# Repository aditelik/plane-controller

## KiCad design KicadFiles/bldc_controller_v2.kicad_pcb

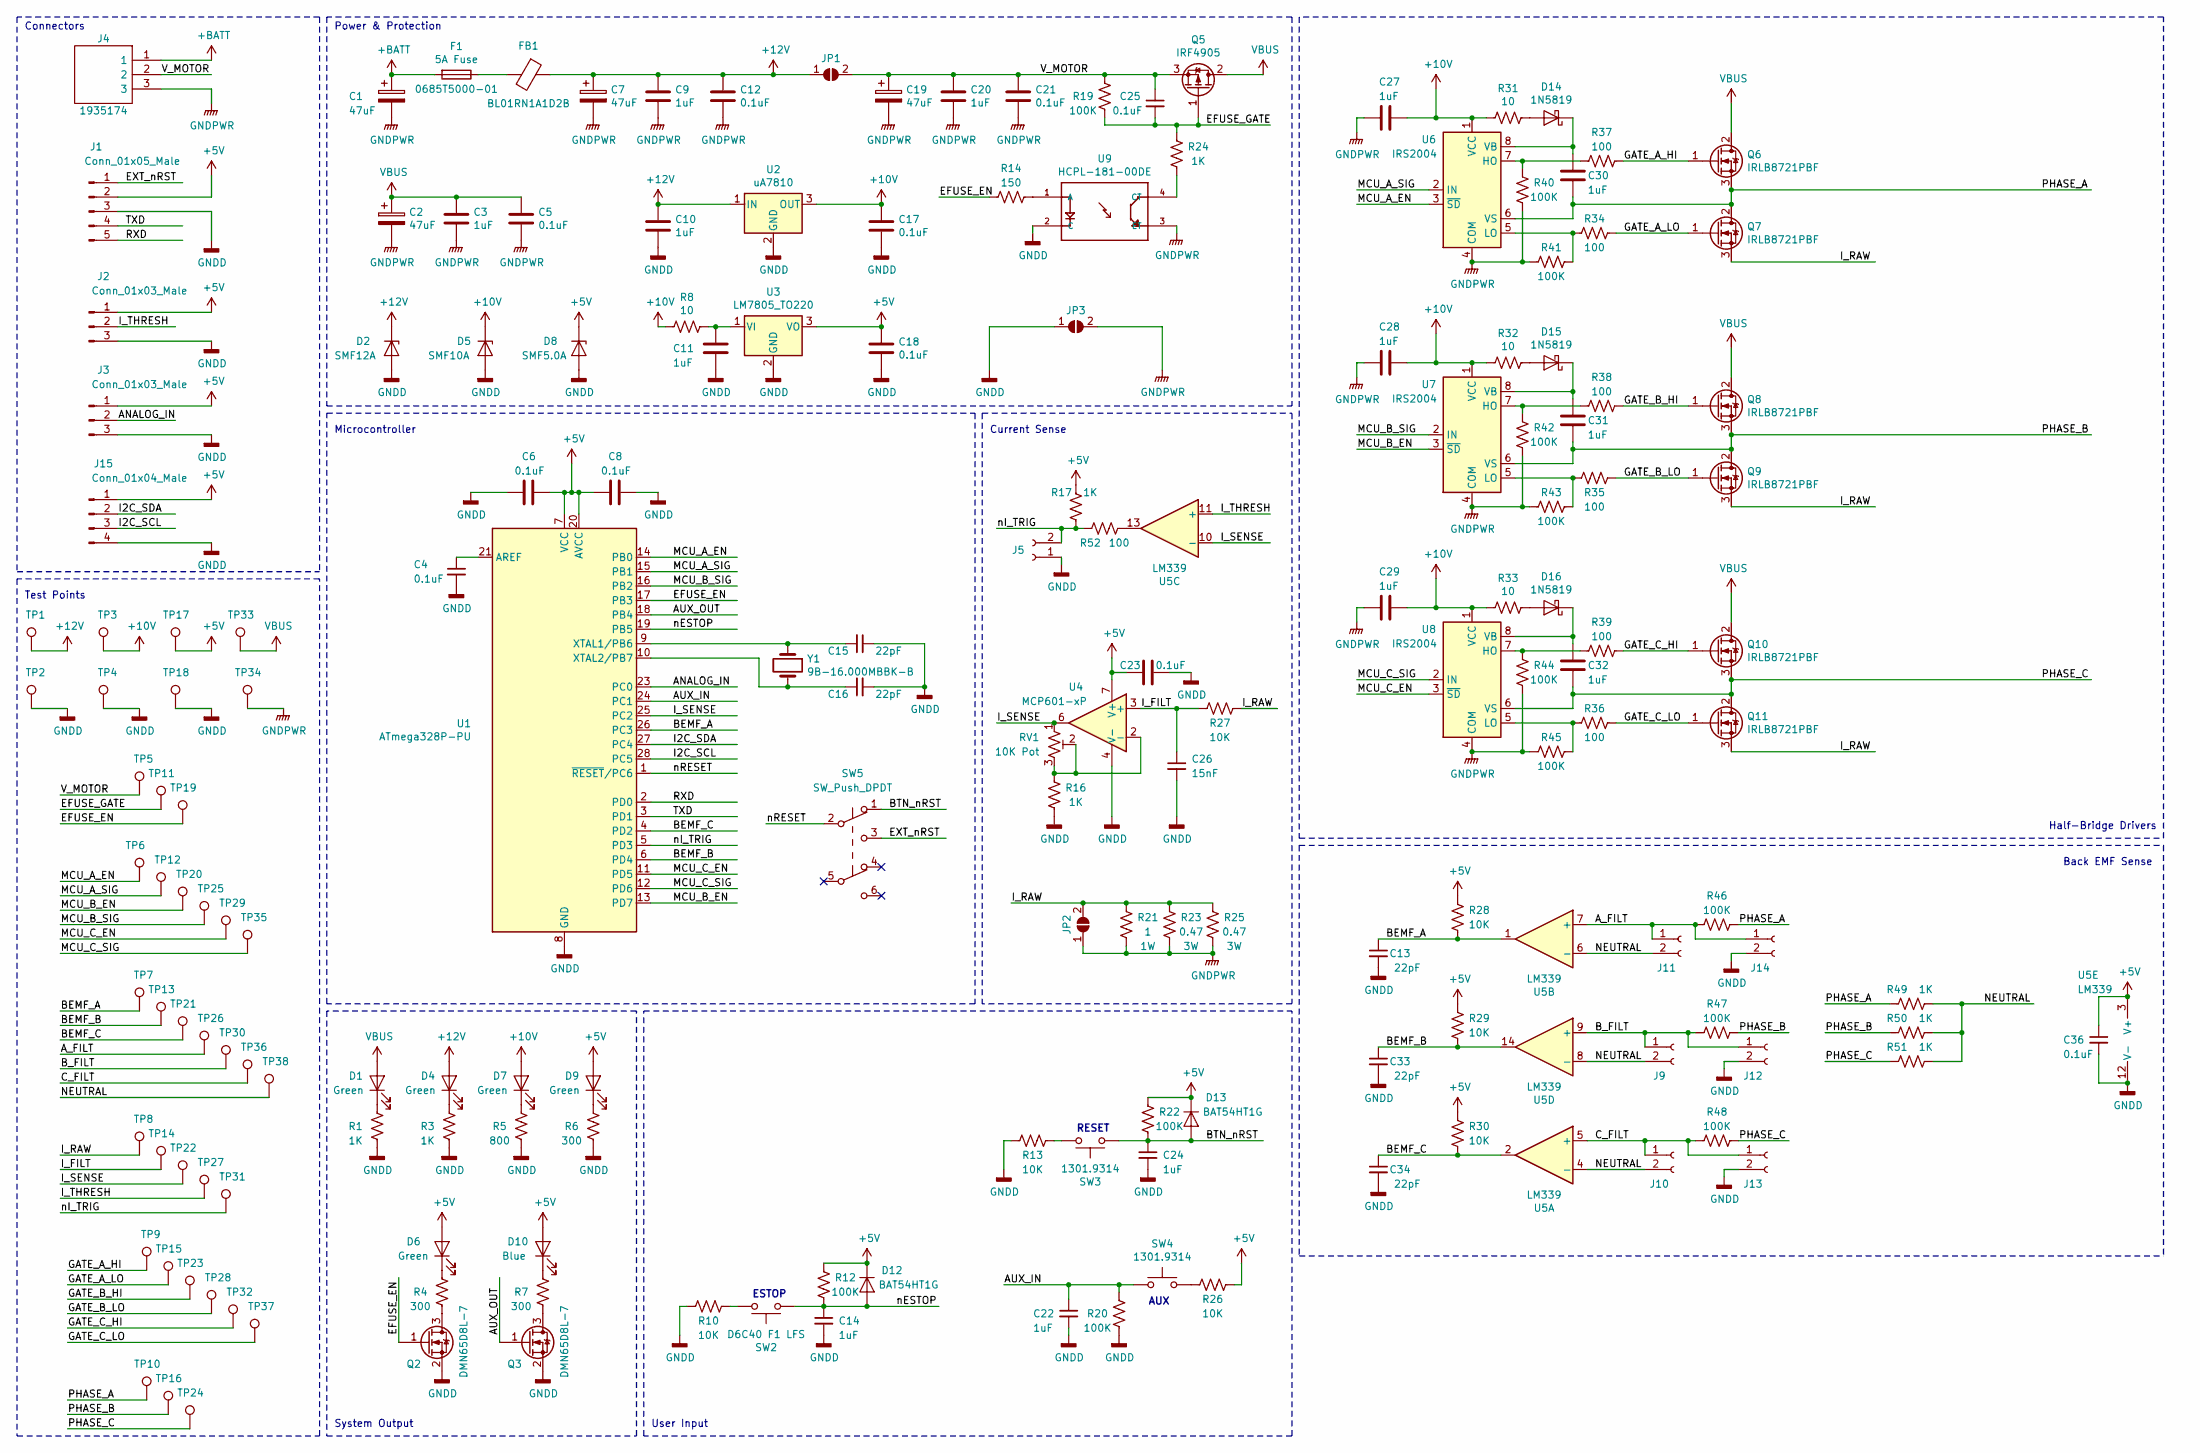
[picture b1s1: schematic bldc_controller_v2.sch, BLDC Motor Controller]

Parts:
C1, C2, C7, C19: 47uF; CP_Radial_D5.0mm_P2.00mm
C3, C9, C10, C11, C14, C20, C22, C24, C27, C28, C29, C30, C31, C32: 1uF; C_0805_2012Metric_Pad1.15x1.40mm_HandSolder
C4, C5, C6, C8, C12, C17, C18, C21, C23, C25, C36: 0.1uF; C_0805_2012Metric_Pad1.15x1.40mm_HandSolder
C13, C15, C16, C33, C34: 22pF; C_0805_2012Metric_Pad1.15x1.40mm_HandSolder
C26: 15nF; C_0805_2012Metric_Pad1.15x1.40mm_HandSolder
D1, D4, D7, D9: LTST-C171GKT; LED_0805_2012Metric_Pad1.15x1.40mm_HandSolder
D2: SMF12A; D_SOD-123F
D5: SMF10A; D_SOD-123F
D6: LTST-C171KRKT; LED_0805_2012Metric_Pad1.15x1.40mm_HandSolder
D8: SMF5.0A; D_SOD-123F
D10: LTST-C171TBKT; LED_0805_2012Metric_Pad1.15x1.40mm_HandSolder
D12, D13: BAT54HT1G; D_SOD-323_HandSoldering
D14, D15, D16: 1N5819; D_SOD-123
F1: 5A Fuse; Fuse_1206_3216Metric_Pad1.42x1.75mm_HandSolder; Part Number 0685T5000-01
FB1: BL01RN1A1D2B; Ferrite_Bead_TH
J1: Conn_01x05_Male; PinHeader_1x05_P2.54mm_Vertical
J2, J3: Conn_01x03_Male; PinHeader_1x03_P2.54mm_Vertical
J4: 1935174; SHDR3W110P0X500_1X3_1500X900X1140P; Mouser Part Number 651-1935174
J5, J9, J10, J11, J12, J13, J14: Conn_01x02_Female; PinSocket_1x02_P2.54mm_Vertical
J15: Conn_01x04_Male; PinHeader_1x04_P2.54mm_Vertical
JP1, JP2, JP3: SolderJumper_2_Open; Solder_Jumper_2_Pin_5A
Q2, Q3: DMN65D8L-7; SOT-23
Q5: IRF4905; TO-220-3_Vertical
Q6, Q7, Q8, Q9, Q10, Q11: IRLB8721PBF; TO-220-3_Vertical
R1, R3, R16, R17, R24, R49, R50, R51: 1K; R_0805_2012Metric_Pad1.15x1.40mm_HandSolder
R4, R6, R7: 300; R_0805_2012Metric_Pad1.15x1.40mm_HandSolder
R5: 800; R_0805_2012Metric_Pad1.15x1.40mm_HandSolder
R8, R31, R32, R33: 10; R_0805_2012Metric_Pad1.15x1.40mm_HandSolder
R10, R13, R26, R27, R28, R29, R30: 10K; R_0805_2012Metric_Pad1.15x1.40mm_HandSolder
R12, R19, R20, R22, R40, R41, R42, R43, R44, R45, R46, R47, R48: 100K; R_0805_2012Metric_Pad1.15x1.40mm_HandSolder
R14: 150; R_0805_2012Metric_Pad1.15x1.40mm_HandSolder
R21: 1; Power_Resistor_TH
R23, R25: 0.47; Power_Resistor_TH
R34, R35, R36, R37, R38, R39, R52: 100; R_0805_2012Metric_Pad1.15x1.40mm_HandSolder
RV1: 10K Pot; Trimmer_Pot_SM
SW2: D6C40 F1 LFS; Pushbutton_Switch_TH
SW3, SW4: 1301.9314; Tactile_Switch_SM
SW5: SW_Push_DPDT; Slide_Switch_DPDT_SMD
TP1, TP3, TP5, TP6, TP7, TP8, TP9, TP10, TP11, TP12, TP13, TP14, TP15, TP16, TP17, TP19, TP20, TP21, TP22, TP23, TP24, TP25, TP26, TP27, TP28, TP29, TP30, TP31, TP32, TP33, TP35, TP36, TP37, TP38: TestPoint; TestPoint_THTPad_1.0x1.0mm_Drill0.5mm
TP2, TP4, TP18, TP34: TestPoint; TestPoint_Keystone_5000-5004_Miniature
U1: ATmega328P-PU; DIP-28_W7.62mm
U2: uA7810; TO-220-3_Vertical
U3: LM7805_TO220; TO-220-3_Vertical
U4: MCP601-xP; DIP-8_W7.62mm
U5: LM339; DIP-14_W7.62mm
U6, U7, U8: IRS2004; DIP-8_W7.62mm
U9: HCPL-181-00DE; SOIC254P700X220-4N
Y1: 9B-16.000MBBK-B; Crystal_16MHz_TH

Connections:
+5V: C6.2, C8.1, C18.1, C23.1, C36.1, D6.2 (A), D8.1 (K), D9.2 (A), D10.2 (A), D12.1 (K), D13.1 (K), J1.2, J2.1, J3.1, J15.1, R12.1, R17.1, R22.1, R26.1, R28.1, R29.1, R30.1, TP17.1, U1.7 (VCC), U1.20 (AVCC), U3.3 (VO), U4.7 (V+), U5.3 (V+)
+10V: C17.1, C27.2, C28.2, C29.2, D5.1 (K), D7.2 (A), R8.2, R31.2, R32.2, R33.2, TP3.1, U2.3 (OUT), U6.1 (VCC), U7.1 (VCC), U8.1 (VCC)
+12V: C7.1, C9.1, C10.1, C12.1, D2.1 (K), D4.2 (A), FB1.1, JP1.1 (A), TP1.1, U2.1 (IN)
+BATT: C1.1, F1.2, J4.1
/ANALOG_IN: J3.2, U1.23 (PC0)
/AUX_IN: C22.1, R20.1, SW4.1, U1.24 (PC1)
/AUX_OUT: Q3.1 (G), U1.18 (PB4)
/A_FILT: J11.1, J14.1, R46.2, TP26.1, U5.7 (+)
/BEMF_A: C13.1, R28.2, TP7.1, U1.26 (PC3), U5.1
/BEMF_B: C33.1, R29.2, TP13.1, U1.6 (PD4), U5.14
/BEMF_C: C34.1, R30.2, TP21.1, U1.4 (PD2), U5.2
/BTN_nRST: C24.1, D13.2 (A), R22.2, SW3.1, SW5.1 (A)
/B_FILT: J9.1, J12.1, R47.2, TP30.1, U5.9 (+)
/C_FILT: J10.1, J13.1, R48.2, TP36.1, U5.5 (+)
/EFUSE_EN: Q2.1 (G), R14.2, TP19.1, U1.17 (PB3)
/EFUSE_GATE: C25.2, Q5.1 (G), R19.2, R24.1, TP11.1
/EXT_nRST: J1.1, SW5.3 (C)
/GATE_A_HI: Q6.1 (G), R37.1, TP9.1
/GATE_A_LO: Q7.1 (G), R34.1, TP15.1
/GATE_B_HI: Q8.1 (G), R38.1, TP23.1
/GATE_B_LO: Q9.1 (G), R35.1, TP28.1
/GATE_C_HI: Q10.1 (G), R39.1, TP32.1
/GATE_C_LO: Q11.1 (G), R36.1, TP37.1
/I2C_SCL: J15.3, U1.28 (PC5)
/I2C_SDA: J15.2, U1.27 (PC4)
/I_FILT: C26.1, R27.2, TP14.1, U4.3 (+)
/I_RAW: JP2.2 (B), Q7.3 (S), Q9.3 (S), Q11.3 (S), R21.1, R23.1, R25.1, R27.1, TP8.1
/I_SENSE: RV1.1, TP22.1, U1.25 (PC2), U4.6, U5.10 (-)
/I_THRESH: J2.2, TP27.1, U5.11 (+)
/MCU_A_EN: TP6.1, U1.14 (PB0), U6.3 (~SD)
/MCU_A_SIG: TP12.1, U1.15 (PB1), U6.2 (IN)
/MCU_B_EN: TP20.1, U1.13 (PD7), U7.3 (~SD)
/MCU_B_SIG: TP25.1, U1.16 (PB2), U7.2 (IN)
/MCU_C_EN: TP29.1, U1.11 (PD5), U8.3 (~SD)
/MCU_C_SIG: TP35.1, U1.12 (PD6), U8.2 (IN)
/NEUTRAL: J9.2, J10.2, J11.2, R49.1, R50.1, R51.1, TP38.1, U5.4 (-), U5.6 (-), U5.8 (-)
/PHASE_A: C30.2, Q6.3 (S), Q7.2 (D), R46.1, R49.2, TP10.1, U6.6 (VS)
/PHASE_B: C31.2, Q8.3 (S), Q9.2 (D), R47.1, R50.2, TP16.1, U7.6 (VS)
/PHASE_C: C32.2, Q10.3 (S), Q11.2 (D), R48.1, R51.2, TP24.1, U8.6 (VS)
/RXD: J1.5, U1.2 (PD0)
/TXD: J1.4, U1.3 (PD1)
/V_MOTOR: C19.1, C20.1, C21.1, C25.1, J4.2, JP1.2 (B), Q5.3 (S), R19.1, TP5.1
/nESTOP: C14.1, D12.2 (A), R12.2, SW2.1, U1.19 (PB5)
/nI_TRIG: J5.2, R17.2, R52.2, TP31.1, U1.5 (PD3)
/nRESET: SW5.2 (B), U1.1 (~RESET~/PC6)
GNDD: C4.2, C6.1, C8.2, C10.2, C11.2, C13.2, C14.2, C15.1, C16.2, C17.2, C18.2, C22.2, C23.2, C24.2, C26.2, C33.2, C34.2, C36.2, D2.2 (A), D5.2 (A), D8.2 (A), J1.3, J2.3, J3.3, J5.1, J12.2, J13.2, J14.2, J15.4, JP3.1 (A), Q2.2 (S), Q3.2 (S), R1.2, R3.2, R5.2, R6.2, R10.2, R13.2, R16.2, R20.2, TP2.1, TP4.1, TP18.1, U1.8 (GND), U1.22 (GND), U2.2 (GND), U3.2 (GND), U4.4 (V-), U5.12 (V-), U9.2 (C)
GNDPWR: C1.2, C2.2, C3.2, C5.2, C7.2, C9.2, C12.2, C19.2, C20.2, C21.2, C27.1, C28.1, C29.1, J4.3, JP2.1 (A), JP3.2 (B), R21.2, R23.2, R25.2, R40.2, R41.2, R42.2, R43.1, R44.1, R45.2, TP34.1, U6.4 (COM), U7.4 (COM), U8.4 (COM), U9.3 (ET)
unnamed: C4.1, U1.21 (AREF)
unnamed: C11.1, R8.1, U3.1 (VI)
unnamed: C15.2, U1.9 (XTAL1/PB6), Y1.1
unnamed: C16.1, U1.10 (XTAL2/PB7), Y1.2
unnamed: C30.1, D14.1 (K), U6.8 (VB)
unnamed: C31.1, D15.1 (K), U7.8 (VB)
unnamed: C32.1, D16.1 (K), U8.8 (VB)
unnamed: D1.1 (K), R1.1
unnamed: D4.1 (K), R3.1
unnamed: D6.1 (K), R4.1
unnamed: D7.1 (K), R5.1
unnamed: D9.1 (K), R6.1
unnamed: D10.1 (K), R7.1
unnamed: D14.2 (A), R31.1
unnamed: D15.2 (A), R32.1
unnamed: D16.2 (A), R33.1
unnamed: F1.1, FB1.2
unnamed: Q2.3 (D), R4.2
unnamed: Q3.3 (D), R7.2
unnamed: R10.1, SW2.2
unnamed: R13.1, SW3.2
unnamed: R14.1, U9.1 (A)
unnamed: R16.1, RV1.2, RV1.3, U4.2 (-)
unnamed: R24.2, U9.4 (CT)
unnamed: R26.2, SW4.2
unnamed: R34.2, R41.1, U6.5 (LO)
unnamed: R35.2, R43.2, U7.5 (LO)
unnamed: R36.2, R45.1, U8.5 (LO)
unnamed: R37.2, R40.1, U6.7 (HO)
unnamed: R38.2, R42.1, U7.7 (HO)
unnamed: R39.2, R44.2, U8.7 (HO)
unnamed: R52.1, U5.13
VBUS: C2.1, C3.1, C5.1, D1.2 (A), Q5.2 (D), Q6.2 (D), Q8.2 (D), Q10.2 (D), TP33.1

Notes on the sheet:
Power & Protection
Half-Bridge Drivers
Back EMF Sense
Microcontroller
ESTOP
User Input
AUX
RESET
System Output
Current Sense
Test Points
Connectors

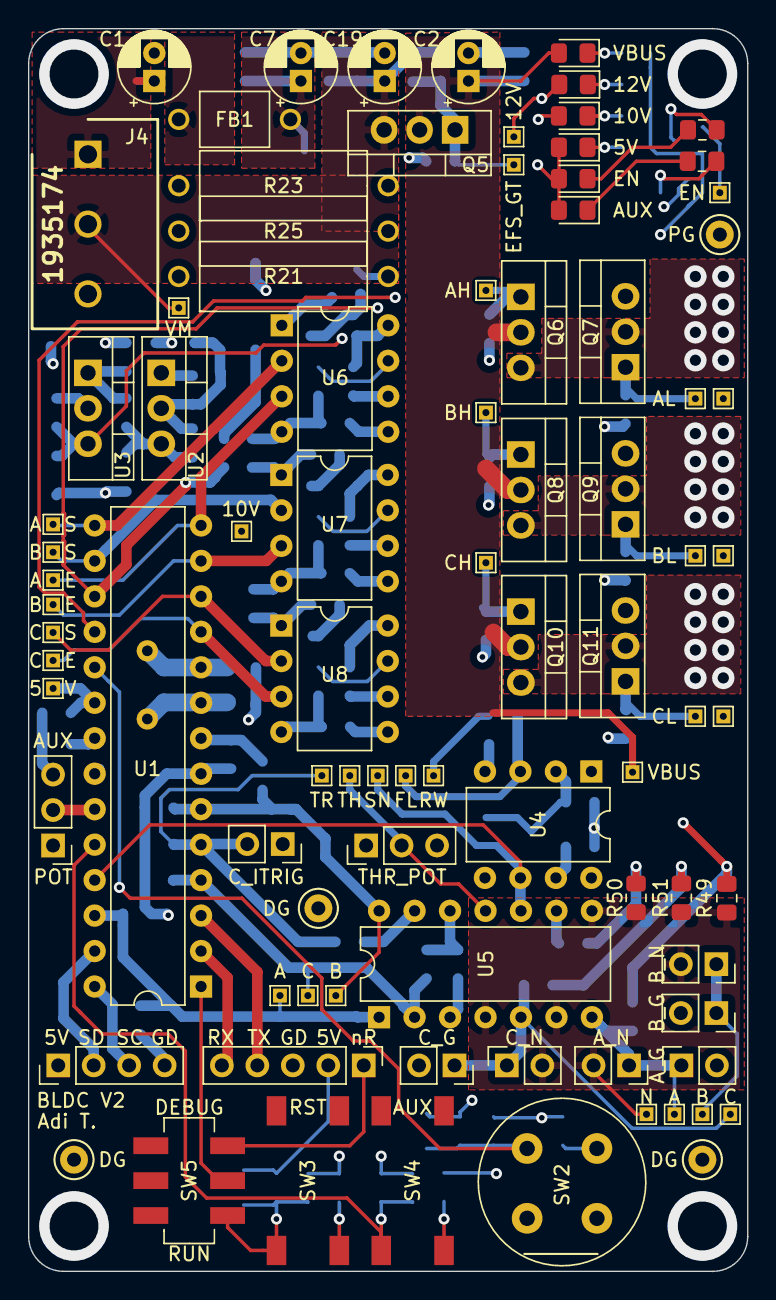
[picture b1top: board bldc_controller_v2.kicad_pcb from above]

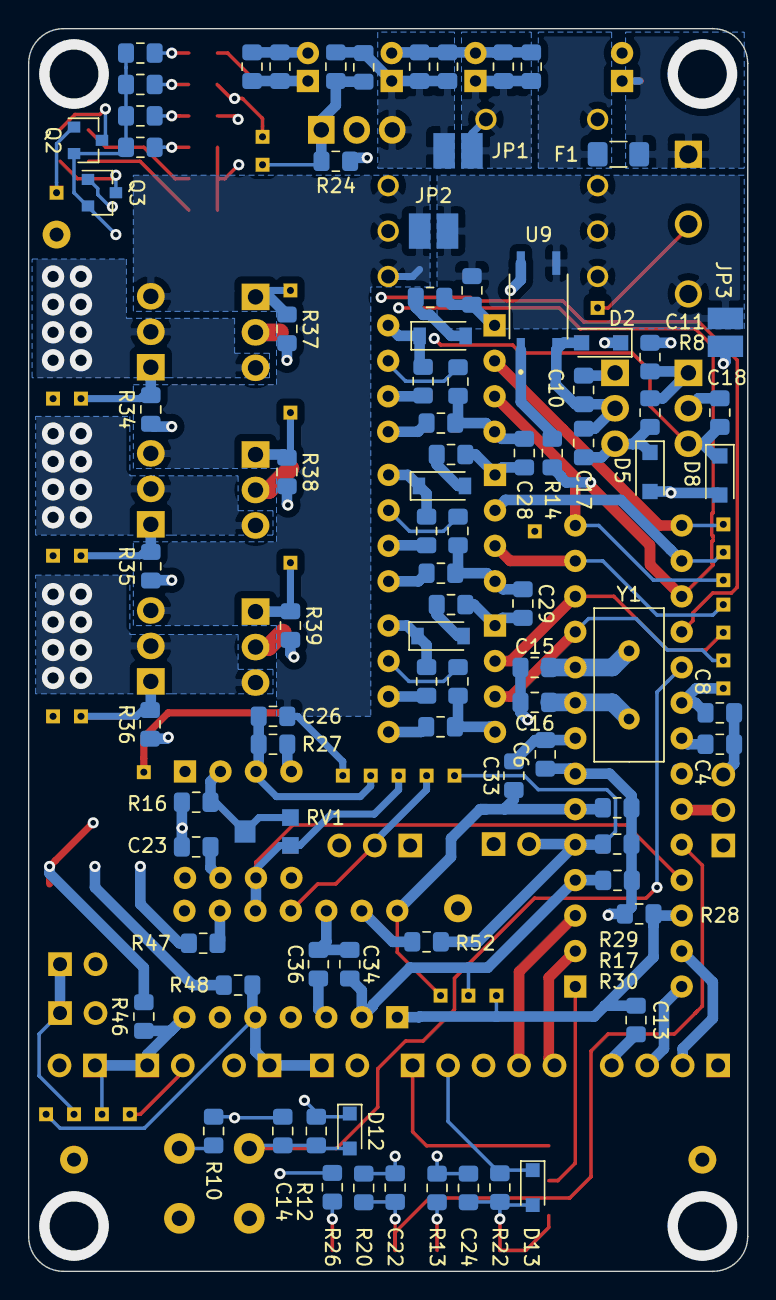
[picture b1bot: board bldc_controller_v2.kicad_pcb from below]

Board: 4 copper layers, 51.5 x 89.0 mm, 175 parts (87 on the bottom side), 80 nets.

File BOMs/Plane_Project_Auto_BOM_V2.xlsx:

Reference | Value | Description
C1 | 47uF | Polarized capacitor
C10 | 1uF | Unpolarized capacitor
C11 | 1uF | Unpolarized capacitor
C12 | 0.1uF | Unpolarized capacitor
C14 | 1uF | Unpolarized capacitor, small symbol
C15 | 22pF | Unpolarized capacitor, small symbol
C16 | 22pF | Unpolarized capacitor, small symbol
C17 | 0.1uF | Unpolarized capacitor
C18 | 0.1uF | Unpolarized capacitor
C19 | 47uF | Polarized capacitor
C2 | 47uF | Polarized capacitor
C20 | 1uF | Unpolarized capacitor
C21 | 0.1uF | Unpolarized capacitor
C22 | 1uF | Unpolarized capacitor, small symbol
C23 | 0.1uF | Unpolarized capacitor
C24 | 1uF | Unpolarized capacitor, small symbol
C25 | 0.1uF | Unpolarized capacitor, small symbol
C26 | 15nF | Unpolarized capacitor, small symbol
C27 | 0.1uF | Unpolarized capacitor
C28 | 0.1uF | Unpolarized capacitor
C29 | 0.1uF | Unpolarized capacitor
C3 | 1uF | Unpolarized capacitor
C30 | 1uF | Unpolarized capacitor
C31 | 1uF | Unpolarized capacitor
C32 | 1uF | Unpolarized capacitor
C36 | 0.1uF | Unpolarized capacitor, small symbol
C4 | 0.1uF | Unpolarized capacitor, small symbol
C5 | 0.1uF | Unpolarized capacitor
C6 | 0.1uF | Unpolarized capacitor
C7 | 47uF | Polarized capacitor
C8 | 0.1uF | Unpolarized capacitor
C9 | 1uF | Unpolarized capacitor
D1 | LTST-C171GKT | Light emitting diode, Green
D10 | LTST-C171TBKT | Light emitting diode, Blue
D12 | BAT54HT1G | 100V 0.3A Small Signal Fast Switching Diode, DO-35
D13 | BAT54HT1G | 100V 0.3A Small Signal Fast Switching Diode, DO-35
D14 | 1N5819 | 30V 1A Schottky Barrier Rectifier Diode, DO-41
D15 | 1N5819 | 30V 1A Schottky Barrier Rectifier Diode, DO-41
D16 | 1N5819 | 30V 1A Schottky Barrier Rectifier Diode, DO-41
D2 | SMF12A | Zener diode
D4 | LTST-C171GKT | Light emitting diode, Green
D5 | SMF10A | Zener diode
D6 | LTST-C171KRKT | Light emitting diode, Green
D7 | LTST-C171GKT | Light emitting diode, Green
D8 | SMF5.0A | Zener diode
D9 | LTST-C171GKT | Light emitting diode, Green
F1 | 5A Fuse | Fuse
FB1 | BL01RN1A1D2B | Ferrite bead
J4 | 1935174 | 3 WAY SCREW TERMINAL BLOCK 5MM PITCH Phoenix Contact Non-Fused Terminal Block
Q10 | IRLB8721PBF | 62A Id, 30V Vds, N-Channel MOSFET, TO-220
Q11 | IRLB8721PBF | 62A Id, 30V Vds, N-Channel MOSFET, TO-220
Q2 | DMN65D8L-7 | 0.21A Id, 60V Vds, N-Channel MOSFET, SOT-23
Q3 | DMN65D8L-7 | 0.21A Id, 60V Vds, N-Channel MOSFET, SOT-23
Q5 | IRF4905 | -74A Id, -55V Vds, Single P-Channel HEXFET Power MOSFET, 20mOhm Ron, TO-220AB
Q6 | IRLB8721PBF | 62A Id, 30V Vds, N-Channel MOSFET, TO-220
Q7 | IRLB8721PBF | 62A Id, 30V Vds, N-Channel MOSFET, TO-220
Q8 | IRLB8721PBF | 62A Id, 30V Vds, N-Channel MOSFET, TO-220
Q9 | IRLB8721PBF | 62A Id, 30V Vds, N-Channel MOSFET, TO-220
R1 | 1K | Resistor, US symbol
R10 | 10K | Resistor, US symbol
R12 | 100K | Resistor, US symbol
R13 | 10K | Resistor, US symbol
R14 | 150 | Resistor, US symbol
R16 | 1K | Resistor, US symbol
R17 | 1K | Resistor, US symbol
R19 | 100K | Resistor, US symbol
R20 | 100K | Resistor, US symbol
R21 | 1 | Resistor, US symbol
R22 | 100K | Resistor, US symbol
R23 | 0.47 | Resistor, US symbol
R24 | 1K | Resistor, US symbol
R25 | 0.47 | Resistor, US symbol
R26 | 10K | Resistor, US symbol
R27 | 10K | Resistor, US symbol
R28 | 10K | Resistor, US symbol
R29 | 10K | Resistor, US symbol
R3 | 1K | Resistor, US symbol
R30 | 10K | Resistor, US symbol
R31 | 10 | Resistor, US symbol
R32 | 10 | Resistor, US symbol
R33 | 10 | Resistor, US symbol
R34 | 10 | Resistor, US symbol
R35 | 10 | Resistor, US symbol
R36 | 10 | Resistor, US symbol
R37 | 10 | Resistor, US symbol
R38 | 10 | Resistor, US symbol
R39 | 10 | Resistor, US symbol
R4 | 300 | Resistor, US symbol
R40 | 100K | Resistor, US symbol
R41 | 100K | Resistor, US symbol
R42 | 100K | Resistor, US symbol
R43 | 100K | Resistor, US symbol
R44 | 100K | Resistor, US symbol
R45 | 100K | Resistor, US symbol
R46 | 100K | Resistor, US symbol
R47 | 100K | Resistor, US symbol
R48 | 100K | Resistor, US symbol
R49 | 10K | Resistor, US symbol
R5 | 800 | Resistor, US symbol
R50 | 10K | Resistor, US symbol
R51 | 10K | Resistor, US symbol
R52 | 100 | Resistor, US symbol
R6 | 300 | Resistor, US symbol
R7 | 300 | Resistor, US symbol
R8 | 10 | Resistor, US symbol
RV1 | 10K Pot | Trim-potentiometer, US symbol
SW2 | D6C40 F1 LFS | Push button switch, generic, two pins
SW3 | 1301.9314 | Push button switch, generic, two pins
SW4 | 1301.9314 | Push button switch, generic, two pins
SW5 | SW_Push_DPDT | Momentary Switch, dual pole double throw
U1 | ATmega328P-PU | 20MHz, 32kB Flash, 2kB SRAM, 1kB EEPROM, DIP-28
U2 | uA7810 | Positive 1A 35V Linear Regulator, Fixed Output 10V, TO-220/TO-263
U3 | LM7805_TO220 | Positive 1A 35V Linear Regulator, Fixed Output 5V, TO-220
U4 | MCP601-xP | Single 2.7V to 6.0V Single Supply CMOS Op Amps, DIP-8
U5 | LM339 | Quad Differential Comparators, DIP-14/SOIC-14/SSOP-14
U6 | IRS2004 | Half-Bridge Driver, 200V, 290/600mA, PDIP-8/SOIC-8
U7 | IRS2004 | Half-Bridge Driver, 200V, 290/600mA, PDIP-8/SOIC-8
U8 | IRS2004 | Half-Bridge Driver, 200V, 290/600mA, PDIP-8/SOIC-8
U9 | HCPL-181-00DE
Y1 | 9B-16.000MBBK-B | 16 MHz Crystal

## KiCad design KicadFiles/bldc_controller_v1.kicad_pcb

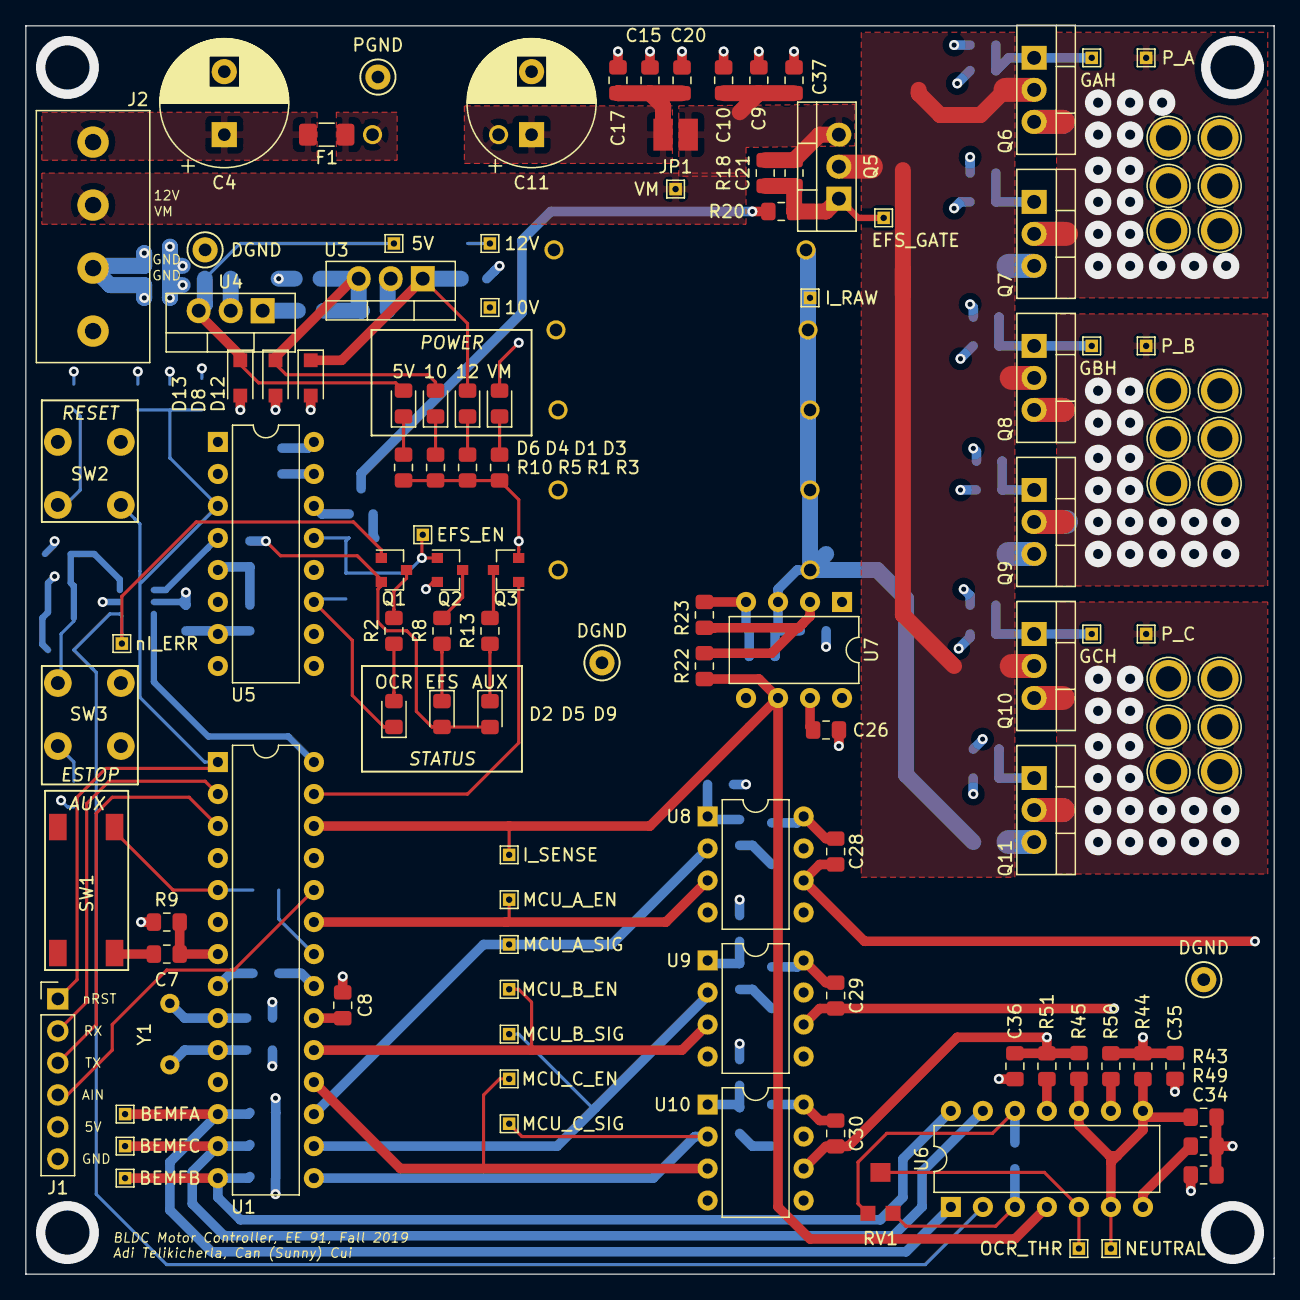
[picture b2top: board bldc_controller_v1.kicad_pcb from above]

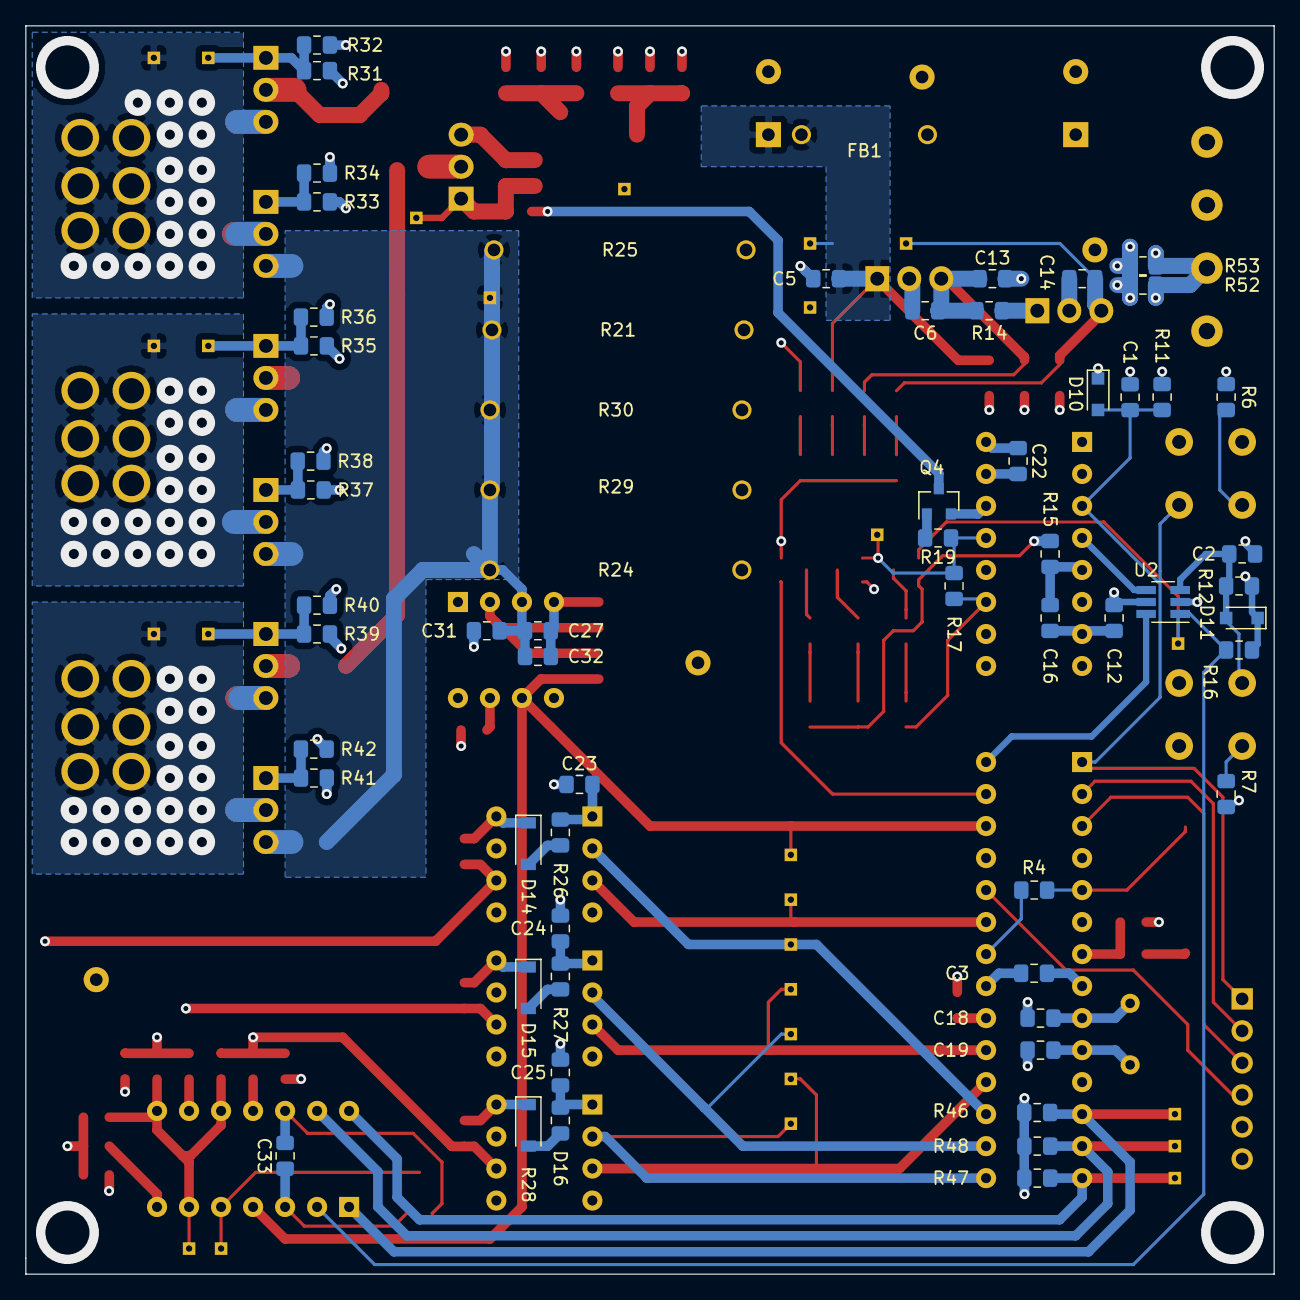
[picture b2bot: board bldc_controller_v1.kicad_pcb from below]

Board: 4 copper layers, 99.1 x 99.1 mm, 166 parts (62 on the bottom side), 79 nets.

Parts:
C1, C2: 10uF; C_0805_2012Metric_Pad1.15x1.40mm_HandSolder
C3, C7, C8, C12, C13, C14, C20, C22, C23, C24, C25, C26, C33, C37: 0.1uF; C_0805_2012Metric_Pad1.15x1.40mm_HandSolder
C4, C11: 47uF; CP_Radial_D10.0mm_P5.00mm
C5: 0.33uF; C_0805_2012Metric_Pad1.15x1.40mm_HandSolder
C6: 0.22uF; C_0805_2012Metric_Pad1.15x1.40mm_HandSolder
C9, C15: 22uF; C_0805_2012Metric_Pad1.15x1.40mm_HandSolder
C10, C16, C17, C21: 1uF; C_0805_2012Metric_Pad1.15x1.40mm_HandSolder
C18, C19: 22pF; C_0805_2012Metric_Pad1.15x1.40mm_HandSolder
C27: 10nF; C_0805_2012Metric_Pad1.15x1.40mm_HandSolder
C28, C29, C30: 22nF; C_0805_2012Metric_Pad1.15x1.40mm_HandSolder
C31: 1nF; C_0805_2012Metric_Pad1.15x1.40mm_HandSolder
C32: 100pF; C_0805_2012Metric_Pad1.15x1.40mm_HandSolder
C34, C35, C36: 0.47uF; C_0805_2012Metric_Pad1.15x1.40mm_HandSolder
D1, D3, D4, D6: LTST-C171GKT; LED_0805_2012Metric_Pad1.15x1.40mm_HandSolder
D2, D5: LTST-C171KRKT; LED_0805_2012Metric_Pad1.15x1.40mm_HandSolder
D8: SMF10A; D_SOD-123F
D9: LTST-C171TBKT; LED_0805_2012Metric_Pad1.15x1.40mm_HandSolder
D10, D11: BAT54HT1G; D_SOD-323_HandSoldering
D12: SMF12A; D_SOD-123F
D13: SMF5.0A; D_SOD-123F
D14, D15, D16: 1N5819; D_SOD-123
F1: 5A Fuse; Fuse_1206_3216Metric_Pad1.42x1.75mm_HandSolder
FB1: BL01RN1A1D2B; Ferrite_Bead_TH
J1: Conn_01x06_Male; PinHeader_1x06_P2.54mm_Vertical
J2: Screw_Terminal_01x04; Terminal_Block_4Pin_TH
JP1: SolderJumper_2_Open; Solder_Jumper_2_Pin_5A
Q1: 2N7002E; SOT-23
Q2, Q3: DMN65D8L-7; SOT-23
Q4: MMBT3904; SOT-23
Q5: IRF4905; TO-220-3_Vertical
Q6, Q7, Q8, Q9, Q10, Q11: IRLB8721PBF; TO-220-3_Vertical
R1, R3, R9, R16, R20, R46, R47, R48, R49, R50, R51: 1K; R_0805_2012Metric_Pad1.15x1.40mm_HandSolder
R2, R8, R10, R13: 300; R_0805_2012Metric_Pad1.15x1.40mm_HandSolder
R4, R11, R12, R17, R18, R23, R43, R44, R45: 10K; R_0805_2012Metric_Pad1.15x1.40mm_HandSolder
R5: 800; R_0805_2012Metric_Pad1.15x1.40mm_HandSolder
R6, R7: 220; R_0805_2012Metric_Pad1.15x1.40mm_HandSolder
R14, R31, R33, R35, R37, R39, R41: 10; R_0805_2012Metric_Pad1.15x1.40mm_HandSolder
R15, R32, R34, R36, R38, R40, R42: 100K; R_0805_2012Metric_Pad1.15x1.40mm_HandSolder
R19: 3K; R_0805_2012Metric_Pad1.15x1.40mm_HandSolder
R21, R24, R25, R29, R30: 1; Power_Resistor_TH
R22: 40K; R_0805_2012Metric_Pad1.15x1.40mm_HandSolder
R26, R27, R28: 4.7; R_0805_2012Metric_Pad1.15x1.40mm_HandSolder
R52, R53: 0; R_0805_2012Metric_Pad1.15x1.40mm_HandSolder
RV1: 5K; Trimmer_Pot_SM
SW1: 1301.9314; Tactile_Switch_SM
SW2: D6C50 F1 LFS; Pushbutton_Switch_TH
SW3: D6C40 F1 LFS; Pushbutton_Switch_TH
TP1, TP2, TP3, TP4, TP5, TP6, TP7, TP8, TP9, TP10, TP11, TP13, TP14, TP15, TP16, TP19, TP20, TP21, TP22, TP23, TP24, TP25, TP26, TP27, TP28, TP30: TestPoint; TestPoint_THTPad_1.0x1.0mm_Drill0.5mm
TP12, TP17, TP18, TP29: TestPoint; TestPoint_Keystone_5000-5004_Miniature
U1: ATmega328P-PU; DIP-28_W7.62mm
U2: SN74LVC1G11DBVR; SOT-23-6_Handsoldering
U3: uA7810; TO-220-3_Vertical
U4: LM7805_TO220; TO-220-3_Vertical
U5: CD4044BE; DIP-16_W7.62mm
U6: LM339; DIP-14_W7.62mm
U7: MCP601-xP; DIP-8_W7.62mm
U8, U9, U10: IRS2004; DIP-8_W7.62mm
Y1: 9B-16.000MBBK-B; Crystal_16MHz_TH

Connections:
+5V: C7.2, C8.1, C12.1, C14.1, C22.1, C26.1, C33.1, D5.2, D6.2, D9.2, D10.1, D11.1, D13.1, J1.5, Q1.2, R9.1, R11.1, R12.1, R15.1, R16.1, R46.1, R47.1, R48.1, RV1.3, TP27.1, U1.7, U1.20, U2.5, U4.3, U5.16, U6.3, U7.7
+10V: C6.1, C13.1, C23.2, C24.2, C25.2, D4.2, D8.1, R14.2, R26.2, R27.2, R28.2, TP26.1, U3.3, U8.1, U9.1, U10.1
+12V: C5.1, C11.1, C15.1, C17.1, C20.1, D1.2, D12.1, FB1.1, JP1.1, TP25.1, U3.1
+BATT: C4.1, F1.2, J2.1
/ANALOG_IN: J1.4, U1.24
/AUX_IN: R4.1, SW1.1, U1.5
/AUX_OUT: Q3.1, U1.27
/BEMF_A: R46.2, TP13.1, U1.12, U6.1
/BEMF_B: R47.2, TP14.1, U1.14, U6.14
/BEMF_C: R48.2, TP15.1, U1.13, U6.13
/EFUSE_EN: Q2.1, R17.1, R19.2, TP3.1, U5.13
/I_RAW: C27.1, C31.1, C32.1, Q7.3, Q9.3, Q11.3, R21.1, R24.1, R25.1, R29.1, R30.1, TP1.1, U7.3
/I_SENSE: R22.1, TP30.1, U1.26, U6.4, U7.6
/MCU_A_EN: TP19.1, U1.23, U8.3
/MCU_A_SIG: TP22.1, U1.17, U8.2
/MCU_B_EN: TP24.1, U1.19, U9.3
/MCU_B_SIG: TP21.1, U1.16, U9.2
/MCU_C_EN: TP23.1, U1.18, U10.3
/MCU_C_SIG: TP20.1, U1.15, U10.2
/NEUTRAL: R43.1, R44.1, R45.1, TP16.1, U6.6, U6.8, U6.10
/RXD: J1.2, U1.2
/TXD: J1.3, U1.3
/nESTOP: C2.1, D11.2, R12.2, SW3.2, U2.3
/nI_ERR: Q1.1, R16.2, TP2.1, U2.1, U6.2
/nMCU_ERR: U1.28, U2.6
/nRESET: C1.1, D10.2, J1.1, R11.2, SW2.1, U1.1, U5.3
GNDD: C1.2, C2.2, C3.2, C5.2, C6.2, C7.1, C8.2, C12.2, C13.2, C14.2, C16.2, C18.1, C19.2, C22.2, C23.1, C24.1, C25.1, C26.2, C27.2, C31.2, C32.2, C33.2, C34.2, C35.2, C36.2, D2.1, D8.2, D12.2, D13.2, J1.6, Q2.2, Q3.2, Q4.2, R1.2, R3.2, R4.2, R5.2, R6.2, R7.2, R10.2, R17.2, R23.2, R32.2, R34.2, R36.2, R38.2, R40.2, R42.2, R52.2, R53.2, RV1.1, TP12.1, TP17.1, TP29.1, U1.8, U1.22, U2.2, U3.2, U4.2, U5.6, U5.7, U5.8, U5.11, U5.12, U5.14, U5.15, U6.12, U7.4, U8.4, U9.4, U10.4
GNDPWR: C4.2, C9.2, C10.2, C11.2, C15.2, C17.2, C20.2, C37.2, J2.3, J2.4, R21.2, R24.2, R25.2, R29.2, R30.2, R52.1, R53.1, TP18.1
unnamed: C3.1, U1.21
unnamed: C16.1, R15.2, U5.5
unnamed: C18.2, U1.9, Y1.1
unnamed: C19.1, U1.10, Y1.2
unnamed: C21.2, Q5.1, R18.2, R20.1, TP5.1
unnamed: C28.1, D14.1, U8.8
unnamed: C29.1, D15.1, U9.8
unnamed: C30.1, D16.1, U10.8
unnamed: D1.1, R1.1
unnamed: D2.2, R2.2
unnamed: D3.1, R3.1
unnamed: D4.1, R5.1
unnamed: D5.1, R8.1
unnamed: D6.1, R10.1
unnamed: D9.1, R13.1
unnamed: D14.2, R26.1
unnamed: D15.2, R27.1
unnamed: D16.2, R28.1
unnamed: F1.1, FB1.2
unnamed: Q1.3, R2.1
unnamed: Q2.3, R8.2
unnamed: Q3.3, R13.2
unnamed: Q4.1, R19.1
unnamed: Q4.3, R20.2
unnamed: Q6.1, R31.1, R32.1, TP9.1
unnamed: Q7.1, R33.1, R34.1
unnamed: Q8.1, R35.1, R36.1, TP10.1
unnamed: Q9.1, R37.1, R38.1
unnamed: Q10.1, R39.1, R40.1, TP11.1
unnamed: Q11.1, R41.1, R42.1
unnamed: R6.1, SW2.2
unnamed: R7.1, SW3.1
unnamed: R9.2, SW1.2
unnamed: R14.1, U4.1
unnamed: R22.2, R23.1, U7.2
unnamed: R31.2, U8.7
unnamed: R33.2, U8.5
unnamed: R35.2, U9.7
unnamed: R37.2, U9.5
unnamed: R39.2, U10.7
unnamed: R41.2, U10.5
unnamed: R49.2, U6.7
unnamed: R50.2, U6.9
unnamed: R51.2, U6.11
unnamed: RV1.2, TP4.1, U6.5
unnamed: U2.4, U5.4
PhaseA: C28.2, C34.1, Q6.3, Q7.2, R43.2, R49.1, TP6.1, U8.6
PhaseB: C29.2, C35.1, Q8.3, Q9.2, R44.2, R50.1, TP7.1, U9.6
PhaseC: C30.2, C36.1, Q10.3, Q11.2, R45.2, R51.1, TP8.1, U10.6
VBUS: D3.2, Q5.2, Q6.2, Q8.2, Q10.2
Vdrive: C9.1, C10.1, C21.1, C37.1, J2.2, JP1.2, Q5.3, R18.1, TP28.1

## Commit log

2019-12-18 Add BOM and KiCad Files
2019-12-24 Ready for new Digikey BOM
2019-12-24 Updated Some Passives
2019-12-24 Removed DPDT Switch
2019-12-24 Reannotated Schematic and Filtered BEMF
2019-12-26 Reannotated and Cleaned Up Schematic
2019-12-27 Ready For Footprints
2019-12-27 Ready for Parts Placement
2019-12-27 Began Placement
2019-12-27 Finished Placing Major Components
2019-12-27 Cleaned Up Repo
2019-12-28 Added Optoisolator
2019-12-28 Updated Major Parts Placement
2019-12-28 Replaced FB with Jumper
2019-12-28 Updated 5V Regulator
2019-12-29 Updated FET Placement
2019-12-30 Need to Update MCU Signals
2019-12-30 Ready to Route
2019-12-30 Began Routing
2019-12-30 Finished Planes
2019-12-30 Finished First Pass of Routing
2019-12-30 Connected Test Points
2019-12-30 Fixed Unconnected Nets
2019-12-31 Started Fixing Top Silk
2019-12-31 Finished Top Silk
2019-12-31 Compated Power Section
2019-12-31 Fixed Gate Test Points
2019-12-31 Ready for DRC
2019-12-31 Almost Passes DRC
2019-12-31 Generated Gerbers
2020-01-01 Added Potentiometer and Fixed Bottom Planes
2020-01-03 Finished Kicad BOM V2
2020-01-03 Added Digikey BOM V2
2020-01-03 Added Caps to BEMF Lines
2020-01-03 Fixed Charge Pumps and Added Text
2020-01-07 Updated Power Ground
